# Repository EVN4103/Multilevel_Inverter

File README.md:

# 7-Level Cascaded H-Bridge Multilevel Inverter

A 7-Level Cascaded H-Bridge (CHB) Multilevel Inverter designed to generate high-quality AC output using Phase-Shifted Sinusoidal PWM (PS-SPWM) control implemented on an STM32F401 microcontroller.

# Project Overview

This project consists of:

- **Hardware**: Power stage and control PCB designed in KiCad  
- **Firmware**: STM32F401-based inverter control firmware  
- **Control Method**: Phase-Shifted Sinusoidal PWM (PS-SPWM)  
- **Target Applications**: Motor drives, renewable energy systems, medium-voltage inverter systems  

# Hardware

Designed using KiCad (EDA Suite)

# Hardware Features
- 3 Cascaded H-Bridge cells
- 7-level stepped AC output
- Modular and scalable architecture
- Designed for reduced harmonic distortion

# Firmware
Generated using STM32CubeMX  
Developed using STM32CubeIDE  

# Microcontroller
STM32F401CCU6

# Control Strategy
- Phase-Shifted Sinusoidal PWM (PS-SPWM)
- Configurable switching frequency
- Modular control structure

# Key Features

✔ Reduced Total Harmonic Distortion (THD)  
✔ Modular multilevel inverter topology  
✔ Timer-based PWM control  
✔ Scalable to higher voltage levels  
✔ Suitable for renewable and motor drive applications  
✔ Closed-loop voltage control implementation  
✔ FFT-based THD measurement
✔ Over-voltage, under-voltage, and over-current protection

# Prototype Setup

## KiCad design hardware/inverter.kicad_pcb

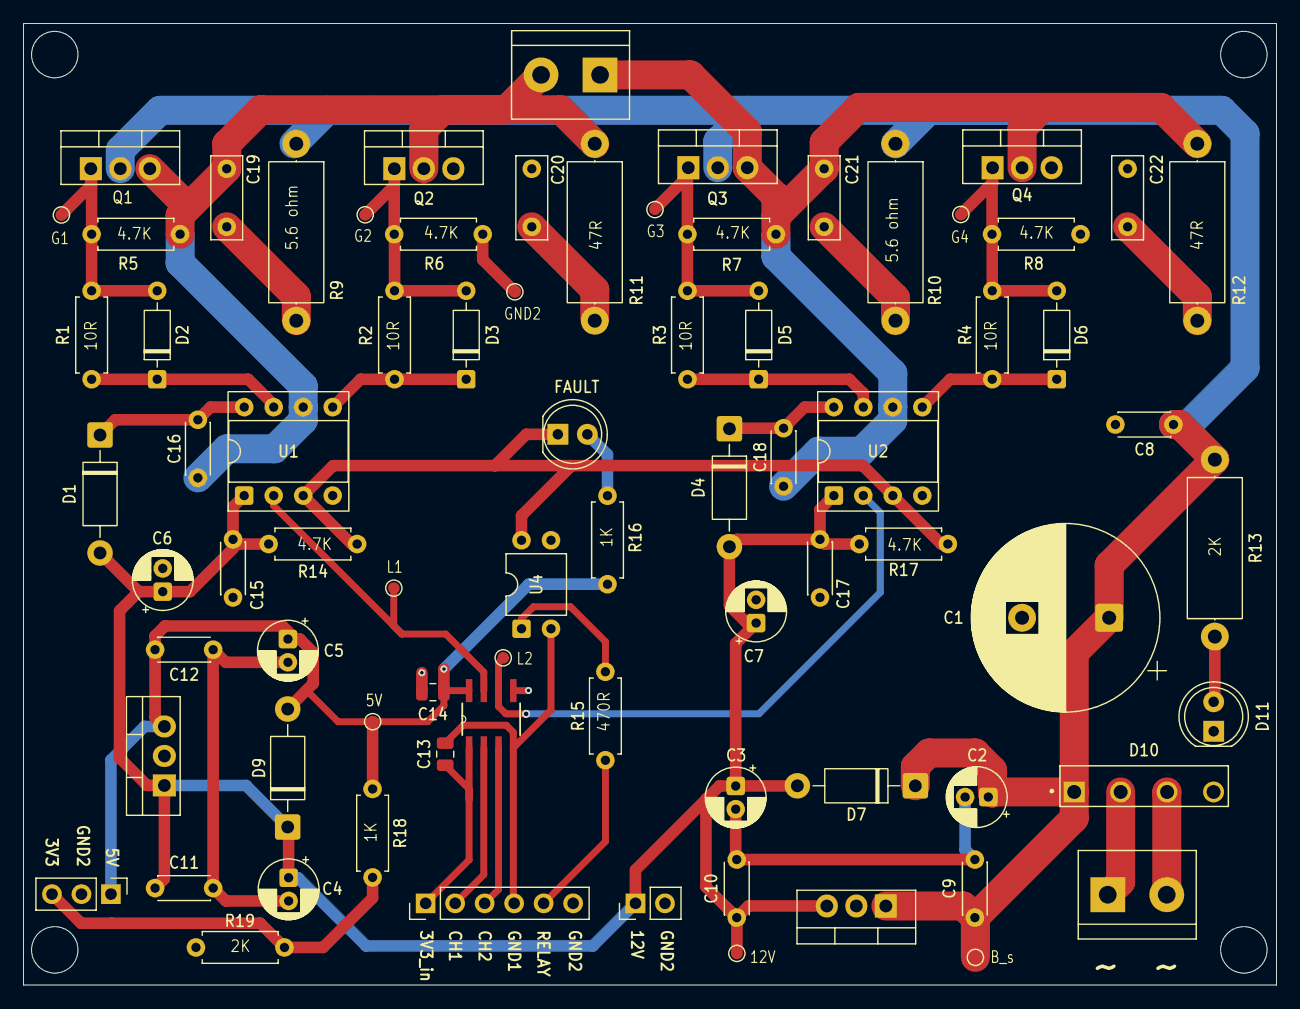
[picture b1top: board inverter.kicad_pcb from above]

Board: 2 copper layers, 107.9 x 82.8 mm, 77 parts (0 on the bottom side), 36 nets.

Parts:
C1: 2200uF/50V; CP_Radial_D16.0mm_P7.50mm
C2, C4: 10uf; CP_Radial_D5.0mm_P2.00mm
C3, C5, C6: 10uF; CP_Radial_D5.0mm_P2.00mm
C7: 10uF e; CP_Radial_D5.0mm_P2.00mm
C8: 0.1uf; C_Disc_D4.3mm_W1.9mm_P5.00mm
C9, C11: 0.22uF; C_Disc_D4.3mm_W1.9mm_P5.00mm
C10, C12: 0.1uF; C_Disc_D4.3mm_W1.9mm_P5.00mm
C13, C14: 0.1uf; C_0805_2012Metric
C15, C17: 0.1uF,X7R; C_Disc_D4.3mm_W1.9mm_P5.00mm
C16, C18: 50V 1uF X7R; C_Disc_D4.3mm_W1.9mm_P5.00mm
C19, C21: 10nF; C_Rect_L7.0mm_W2.5mm_P5.00mm
C20, C22: 3.3nF; C_Rect_L7.0mm_W2.5mm_P5.00mm
D1, D4: SR1100; D_DO-41_SOD81_P10.16mm_Horizontal
D2, D3, D5, D6: 1N4448; D_DO-35_SOD27_P7.62mm_Horizontal
D7, D9: 1N5819; D_DO-41_SOD81_P10.16mm_Horizontal
D8: LED; LED_D5.0mm
D10: KBP208G; SIP350W80P400L1450H1280Q4
D11: LED_G; LED_D5.0mm
J1, J4: Screw_Terminal_01x02; TerminalBlock_bornier-2_P5.08mm
J2: Conn_01x06_Pin; PinHeader_1x06_P2.54mm_Vertical
J3: Conn_01x02_Pin; PinHeader_1x02_P2.54mm_Vertical
J5: Conn_01x03_Pin; PinHeader_1x03_P2.54mm_Vertical
Q1, Q2, Q3, Q4: IRF540N; TO-220-3_Vertical
R1, R2, R3, R4: 10R; R_Axial_DIN0207_L6.3mm_D2.5mm_P7.62mm_Horizontal
R5, R6, R7, R8, R14, R17: 4.7K; R_Axial_DIN0207_L6.3mm_D2.5mm_P7.62mm_Horizontal
R9, R10: 5.6 ohm, 1W; R_Axial_DIN0414_L11.9mm_D4.5mm_P15.24mm_Horizontal
R11, R12: 39 ohm, 1W; R_Axial_DIN0414_L11.9mm_D4.5mm_P15.24mm_Horizontal
R13: 2K; R_Axial_DIN0414_L11.9mm_D4.5mm_P15.24mm_Horizontal
R15: 470; R_Axial_DIN0207_L6.3mm_D2.5mm_P7.62mm_Horizontal
R16: 1K; R_Axial_DIN0207_L6.3mm_D2.5mm_P7.62mm_Horizontal
R18: 1k; R_Axial_DIN0207_L6.3mm_D2.5mm_P7.62mm_Horizontal
R19: 2k; R_Axial_DIN0207_L6.3mm_D2.5mm_P7.62mm_Horizontal
TP1: B_s; TestPoint_Pad_D1.0mm
TP2: 12V; TestPoint_Pad_D1.0mm
TP3: 5V; TestPoint_Pad_D1.0mm
TP4: CH1; TestPoint_Pad_D1.0mm
TP5: CH2; TestPoint_Pad_D1.0mm
TP6: S1; TestPoint_Pad_D1.0mm
TP7: S2; TestPoint_Pad_D1.0mm
TP8: S3; TestPoint_Pad_D1.0mm
TP9: S4; TestPoint_Pad_D1.0mm
TP10: GND2; TestPoint_Pad_D1.0mm
U1, U2: IR2104; DIP-8_W7.62mm_Socket
U3: ADUM1200BRZ-RL7; SOIC127P600X175-8N
U4: PC817; DIP-4_W7.62mm
U5: LM7805_TO220; TO-220-3_Vertical
U6: LM7812_TO220; TO-220-3_Vertical

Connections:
/3.3V MCU: C13.1, J2.1, U3.1 (VDD1)
/5V REG: C5.1, C12.1, C14.1, D9.2 (A), J5.1, R16.2, R18.1, TP3.1, U3.8 (VDD2), U5.3 (VO)
/12V_REG: C3.1, C4.1, C6.1, C7.1, C10.1, C11.1, C15.1, C17.1, D1.2 (A), D4.2 (A), D7.2 (A), D9.1 (K), J3.1, R14.2, R17.2, TP2.1, U1.1 (VCC), U2.1 (VCC), U5.1 (VI), U6.3 (VO)
/AC1: D10.3, J1.2
/AC2: D10.2, J1.1
/BRIDGE+DRIVER/gate_1: D2.2 (A), Q1.1 (G), R1.2, R5.2, TP6.1
/BRIDGE+DRIVER/gate_2: D3.2 (A), Q2.1 (G), R2.2, R6.2, TP7.1
/BRIDGE+DRIVER/gate_3: D5.2 (A), Q3.1 (G), R3.2, R7.2, TP8.1
/BRIDGE+DRIVER/gate_4: D6.2 (A), Q4.1 (G), R4.2, R8.2, TP9.1
/BRIDGE+DRIVER/node_1: C16.2, C19.2, J4.2, Q1.3 (S), Q2.2 (D), R5.1, R11.1, U1.6 (VS)
/BRIDGE+DRIVER/node_2: C18.2, C21.2, J4.1, Q3.3 (S), Q4.2 (D), R7.1, R12.1, U2.6 (VS)
/Bridge_supply: C1.1, C2.1, C8.1, C9.1, D7.1 (K), D10.1, Q1.2 (D), Q3.2 (D), R9.1, R10.1, R13.1, TP1.1, U6.1 (VI)
/Leg_1_in: J2.2, U3.2 (VIA)
/Leg_1_out: TP4.1, U1.2 (IN), U3.7 (VOA)
/Leg_2_in: J2.3, U3.3 (VIB)
/Leg_2_out: TP5.1, U2.2 (IN), U3.6 (VOB)
/SD_in: D8.1 (K), R14.1, R17.1, U1.3 (~SD), U2.3 (~SD), U4.4
/relay_sig_in: J2.5, R15.1
GND1: C13.2, J2.4, U3.4 (GND1), U4.2
GND2: C1.2, C6.2, C7.2, C8.2, C14.2, C15.2, C17.2, C20.2, C22.2, D10.4, D11.1 (K), J2.6, J3.2, J5.2, Q2.3 (S), Q4.3 (S), R6.1, R8.1, R19.2, TP10.1, U1.4 (COM), U2.4 (COM), U3.5 (GND2), U4.3, U5.2 (GND), U6.2 (GND)
unnamed: C2.2, C3.2, C9.2, C10.2
unnamed: C4.2, C5.2, C11.2, C12.2
unnamed: C19.1, R9.2
unnamed: C20.1, R11.2
unnamed: C21.1, R10.2
unnamed: C22.1, R12.2
unnamed: C16.1, D1.1 (K), U1.8 (VB)
unnamed: D2.1 (K), R1.1, U1.7 (HO)
unnamed: D3.1 (K), R2.1, U1.5 (LO)
unnamed: C18.1, D4.1 (K), U2.8 (VB)
unnamed: D5.1 (K), R3.1, U2.7 (HO)
unnamed: D6.1 (K), R4.1, U2.5 (LO)
unnamed: D8.2 (A), R16.1
unnamed: D11.2 (A), R13.2
unnamed: J5.3, R18.2, R19.1
unnamed: R15.2, U4.1

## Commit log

2026-02-27 Initial commit - Added hardware and firmware files
2026-02-27 PCB view updated
2026-02-27 Added PCB layout image
2026-03-17 Added Simulink model for inverter system
2026-03-20 prototype image updated
2026-03-20 Hardware setup and hardware design updated
2026-03-20 Arduino and STM firmware updated
2026-04-04 Updated inverter schematic
2026-04-04 Removed .history folder from tracking
